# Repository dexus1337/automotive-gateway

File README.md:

# Automotive Gateway: Multi-Bus ECU Interface, MitM Filter & Telemetry Board

[-green.svg)]()

An automotive-grade, multi-protocol vehicle network interface, Man-in-the-Middle (MitM) filter, and wireless telemetry gateway. Rather than focusing on CAN alone, this board provides full hardware integration for **all three common automotive ECU communication methods**:
1. **High-Speed CAN (HS-CAN / CAN FD)**
2. **Fault-Tolerant Low-Speed CAN (FT-CAN)**
3. **K-Line / LIN (ISO 9141-2 / ISO 14230 / LIN 2.x)**

All three protocols are driven by two dedicated 32-bit ARM Cortex-M4 microcontrollers and an ESP32 wireless co-processor, featuring dual isolated channels per protocol.

---

## 📑 Table of Contents

- [Overview](#-overview)
- [Operating Modes: Normal vs. MitM](#-operating-modes-normal-vs-mitm)
- [Power Management & Auto-Wake Architecture](#-power-management--auto-wake-architecture)
- [Key Features](#-key-features)
- [System Architecture](#-system-architecture)
- [Hardware & Functional Zones](#-hardware--functional-zones)
- [Pinout & Interface Definitions](#-pinout--interface-definitions)
- [Jumper Configuration Guide](#-jumper-configuration-guide)
- [Bill of Materials (BOM) Summary](#-bill-of-materials-bom-summary)
- [PCB Layout & Physical Specifications](#-pcb-layout--physical-specifications)
- [Getting Started & Flashing Guide](#-getting-started--flashing-guide)
- [Hardware Attribution](#-hardware-attribution)

---

## 🛠 Overview

Modern vehicle architectures rely on three primary communication standards to interconnect Electronic Control Units (ECUs) across various vehicle domains:
- **High-Speed CAN (HS-CAN / CAN FD)**: Up to 1 Mbps (CAN FD capable up to 5 Mbps) for latency-critical powertrain, drivetrain, braking, ABS, and chassis control.
- **Fault-Tolerant Low-Speed CAN (FT-CAN)**: Up to 125 kbps for robust body control, doors, lighting, climate (HVAC), and convenience systems, featuring automatic single-wire fallback upon bus faults.
- **K-Line / LIN (ISO 9141-2 / ISO 14230 / LIN 2.x)**: Bidirectional single-wire 12V automotive bus (up to 20 kbaud) universally used for OBD-II legacy diagnostics, ECU bench reflashing, instrumentation, and LIN sub-busses.

The **Automotive Gateway** provides a unified hardware platform equipped with dedicated transceivers for all three physical layers. It eliminates the need for separate diagnostic interfaces or multiple conversion dongles, serving as a comprehensive tool for active multi-bus communication, real-time message filtering, frame modification, diagnostic proxying, and wireless telemetry streaming via Wi-Fi and Bluetooth BLE.

---

## ⚙️ Operating Modes: Normal vs. MitM

The board features dual physical transceiver channels per communication method (Channel 1 and Channel 2), supporting two primary operating modes:

```
─────────────────────────────────────────────────────────────────────────────────────────────
 Mode 1: Normal Mode (Standalone Additional ECU / Gateway)
 [ Vehicle Network ] ◄──► ( Channel 1 ) ◄──► [ Dual-STM32 + ESP32 ] (Reads & Sends on Busses)

 Mode 2: In-line Man-in-the-Middle Mode (MitM Filter / Message Modification)
 [ Vehicle Network ] ◄──► ( Channel 1 ) ◄──► [ Real-Time Filter ] ◄──► ( Channel 2 ) ◄──► [ Target ECU ]
─────────────────────────────────────────────────────────────────────────────────────────────
```

### 1. Normal Mode (Standalone ECU)
> [!NOTE]
> **There is no listen-only mode.** In Normal Mode, the Automotive Gateway acts as an active, standalone, additional ECU on the vehicle networks.

- **Bi-directional Bus Access**: The gateway actively reads incoming data and transmits outgoing messages on the connected vehicle busses across all three supported physical interfaces (HS-CAN, FT-CAN, and K-Line/LIN).
- **Core Functions**:
  - Functions as an additional standalone ECU node directly participating on the network.
  - Broadcasts custom telemetry, control frames, or simulated sensor messages onto the bus.
  - Sends diagnostic requests (OBD-II, UDS / ISO 14229, KWP2000 / ISO 14230) to other vehicle ECUs and receives responses.
  - Acts as a bi-directional wireless gateway, streaming live multi-bus metrics and receiving remote commands over Wi-Fi (WebSockets, MQTT, REST) or Bluetooth LE.
- **Bus Connectivity**: Connects to the vehicle network via Channel 1 (`CAN-HS1`, `CAN-FT1`, and/or `K-LINE1 Pin 1`). Channel 2 can interface with a second independent vehicle bus, an auxiliary bench network, or remain unpopulated.

### 2. Man-in-the-Middle (MitM) Mode (In-line Filter & Message Modification)
- **Operation**: The gateway is inserted physically in-line between the vehicle wiring harness and a specific target Electronic Control Unit (ECU).
  - **Channel 1 (Network side)**: Connected to the main vehicle bus (`CAN-HS1`, `CAN-FT1`, or `K-LINE1 Pin 1`).
  - **Channel 2 (ECU side)**: Connected directly to the target ECU (`CAN-HS2`, `CAN-FT2`, or `K-LINE1 Pin 2`).
- **Core Functions**:
  - **Message Filtering**: Intercepts bidirectional communications in real time with sub-millisecond determinism to selectively filter out, block, or suppress unwanted messages, diagnostic requests, or forbidden IDs.
  - **Message Modification**: Inspects packets on the fly and modifies payload bytes, alters sensor values (e.g., vehicle speed, odometer, torque parameters), remaps frame IDs, recalculates CRCs/checksums, and retransmits them downstream.
  - **ECU Bench Testing & Security**: Allows fuzzing, spoofing responses, and security validation of a targeted ECU without injecting malformed or test frames into the rest of the vehicle.

---

## ⚡ Power Management & Auto-Wake Architecture

The board features an intelligent automotive power supply designed for both permanent vehicle installation and portable diagnostic use:

```
                        +12V Battery Input (12V1 Pin 1)
                                      │
                         [ D5: SMCJ24CA 24V TVS ]
                                      │
                         [ Q1: AO3401A P-MOSFET ]
                                      │ (12V_Switched)
                                      ▼
                        [ U8: LM2596S-5 Buck Conv ] ──► +5V Rail
                                      │
                        [ U9: AMS1117-3.3 LDO ]    ──► +3.3V Logic Rail
```

### Intelligent Sleep & Auto-Wake Circuit
To prevent 12V battery drain when permanently installed in a vehicle, the module features an ultra-low quiescent sleep circuit:
1. **Sleep State**: The high-side P-channel MOSFET (`Q1`) cuts +12V power to the buck converter (`U8`), completely disabling the 5V and 3.3V rails. The microcontrollers and ESP32 consume **zero current**.
2. **Wake-up Trigger**: The Fault-Tolerant CAN transceiver (`U6`, NXP TJA1055T) remains powered directly from the protected 12V battery rail in ultra-low quiescent standby mode. Upon detecting bus activity on FT-CAN Channel 1, `U6` asserts its `INH` pin HIGH, pulling the gate of N-channel MOSFET `Q2` high via dual Schottky diode `D4`.
3. **Power Latch (Keep-Alive)**: `Q2` activates, pulling `Q1`'s gate low to turn ON the system power rails. Once booted, MCU 1 (`U1`) and MCU 2 (`U2`) assert their respective keep-alive GPIOs (`PC13` via `D3`) to latch power continuously.
4. **Controlled Shutdown**: When vehicle network traffic ceases, the firmware prepares for safe shutdown and de-asserts `PC13`, allowing the board to return to sleep.
5. **Always-On Override (`J3`)**: Installing a jumper on header `J3` (`JP_ALWAYS_ON`) bypasses the auto-wake logic and holds the board permanently powered whenever +12V is present.

---

## ✨ Key Features

- **Dual ARM Cortex-M4 Processing Core**:
  - Two dedicated **STM32F405RGTx** microcontrollers running at **168 MHz** (1 MB Flash, 192 KB SRAM each).
  - **MCU 1 (`U1`)**: Dedicated Low-Speed Fault-Tolerant CAN controller (`CAN1` & `CAN2`).
  - **MCU 2 (`U2`)**: Dedicated High-Speed CAN (`CAN1` & `CAN2`) and Dual K-Line controller (`USART1` & `USART6`).
- **Direct High-Speed Inter-MCU Link**:
  - Dedicated hardware UART bus connecting MCU 1 and MCU 2 (`PC10` / `PC11`) for deterministic cross-bus message passing without co-processor latency.
- **All 3 Common Automotive ECU Physical Layers Supported (Dual Channels Each)**:
  - **High-Speed CAN (HS-CAN / CAN FD)**: 2× NXP `TJA1044GT-3` transceivers (ISO 11898-2:2016, CAN FD ready up to 5 Mbps) with switchable 120 Ω bus termination.
  - **Fault-Tolerant Low-Speed CAN (FT-CAN)**: 2× NXP `TJA1055T/3` transceivers (ISO 11898-3, up to 125 kbps) with single-wire fallback and automatic wake-up signaling.
  - **Dual K-Line / LIN (ISO 9141-2 / ISO 14230 / LIN 2.x)**: 2× NXP `TJA1021xT` transceivers (LIN 2.2A / SAE J2602) supporting OBD-II and KWP2000 diagnostic lines up to 20 kbaud.
- **High-Precision External Quartz Clocking (HSE)**:
  - Dedicated 8.000 MHz SMD-3225 4-pin quartz crystals (`Y1`, `Y2`) with 15 pF C0G load capacitors (`C40`–`C43`) for both STM32F405 MCUs.
  - Automotive-grade $\pm 10\,\text{ppm}$ clock accuracy, eliminating internal RC oscillator frequency drift across automotive temperature ranges.
  - **Zero-Error Baud Rate Timing**: Derives an exact 42 MHz APB1 peripheral clock, achieving $0.000\%$ timing error for the critical **83.3333 kBd** Fault-Tolerant CAN standard ($\text{BRP}=28$, $18\,T_q$, $83.33\%$ sample point) as well as exact bit rates for 100k, 125k, 250k, 500k, and 1 MBd HS-CAN / CAN FD.
- **Wireless Telemetry Co-Processor**:
  - **ESP32-WROOM-32UE** module with 2.4 GHz Wi-Fi (802.11 b/g/n) and Bluetooth v4.2 BR/EDR & BLE.
  - Integrated U.FL external antenna connector for high-gain antenna placement inside vehicle dashboards or engine bays.
  - Dual independent high-speed UART links connecting to MCU 1 and MCU 2.
- **User Interface & Diagnostic Feedback**:
  - Onboard RGB Status LED (`D6`, SMD 1210) driven by ESP32 GPIOs for mode, packet activity, and error signaling.
  - Tactile push buttons for ESP32 hardware `RESET` and `BOOT` (GPIO0).
- **Automotive Protection & Regulation**:
  - Automotive transient voltage suppressor (`D5`, SMCJ24CA bidirectional TVS).
  - P-channel MOSFET (`Q1`, AO3401A) reverse polarity and high-side power switching.
  - 12V Zener (`D1`, MMSZ12T1G) Vgs gate overvoltage clamp.
  - High-efficiency switching buck regulator (`U8`, LM2596S-5, 3A capacity).
  - Low-dropout linear regulator (`U9`, AMS1117-3.3, 1A capacity).
  - Ferrite bead filtering (`FB1`, `FB2`) on analog power supplies (`VDDA`).

---

## 📐 System Architecture

```
                                  +12V AUTOMOTIVE BATTERY (12V1)
                                                │
                          ┌─────────────────────┴─────────────────────┐
                          ▼                                           ▼
             [ SMCJ24CA 24V TVS Clamp ]                  [ AO3401A P-MOSFET Switch ]
                          │                                           │ (12V_Switched)
                          │                                           ▼
                          │                              [ LM2596S-5 Buck Regulator ] ──► +5V Rail
                          │                                           │
                          │                              [ AMS1117-3.3 LDO Regulator] ──► +3.3V Rail
                          │                                           │
         ┌────────────────┴───────────────────────────────────────────┴────────────────────────┐
         │                                                            │                        │
         ▼                                                            ▼                        ▼
┌───────────────────────────────┐               ┌───────────────────────────────┐   ┌──────────────────────┐
│      STM32F405 #1 (MCU 1)     │               │      STM32F405 #2 (MCU 2)     │   │   ESP32-WROOM-32UE   │
│   Low-Speed Fault-Tolerant    │◄─────────────►│     High-Speed CAN & K-Line   │   │   Wireless Gateway   │
│   CAN Controller (168 MHz)    │  Direct UART  │     Controller (168 MHz)      │   │   (Wi-Fi / BT / BLE) │
└──────┬─────────────────┬──────┘   (PC10/PC11) └──────┬─────────────────┬──────┘   └───────┬──────┬───────┘
       │ (CAN1)          │ (CAN2)                      │ (CAN1)          │ (CAN2)           │      │
       ▼                 ▼                             ▼                 ▼                  │      │
 ┌───────────┐     ┌───────────┐                 ┌───────────┐     ┌───────────┐            │      │
 │  TJA1055T │     │  TJA1055T │                 │ TJA1044GT │     │ TJA1044GT │      UART1 │      │ UART2
 │ (FT-CAN1) │     │ (FT-CAN2) │                 │ (HS-CAN1) │     │ (HS-CAN2) │   (PA2/PA3)│      │(PA2/PA3)
 └─────┬─────┘     └─────┬─────┘                 └─────┬─────┘     └─────┬─────┘            │      │
       │                 │                             │                 │                  │      │
       ▼                 ▼                             ▼                 ▼                  │      │
 [  CAN-FT1  ]     [  CAN-FT2  ]                 [  CAN-HS1  ]     [  CAN-HS2  ]            ▼      ▼
 (Channel 1)       (Channel 2)                   (Channel 1)       (Channel 2)          [ Independent ]
  Normal / MitM     Normal / MitM                 Normal / MitM     Normal / MitM       [ UART Links  ]
                                                       │                 │                     │
                                                 ┌─────┴─────┐     ┌─────┴─────┐               ▼
                                                 │JP-CAN-HS1 │     │JP-CAN-HS2 │        [ RGB LED (D6) ]
                                                 │(120Ω Term)│     │(120Ω Term)│        [ GPIO25/26/27 ]
                                                 └───────────┘     └───────────┘
                                                
                                                [ MCU 2 UARTs (USART6 / USART1) ]
                                                               │
                                                   ┌───────────┴───────────┐
                                                   ▼                       ▼
                                             ┌───────────┐           ┌───────────┐
                                             │ TJA1021xT │           │ TJA1021xT │
                                             │ (K-Line 1)│           │ (K-Line 2)│
                                             └─────┬─────┘           └─────┬─────┘
                                                   │                       │
                                                   ▼                       ▼
                                             [        K-LINE1 Header       ]
                                             [  Pin 1: Ch 1  |  Pin 2: Ch 2]
                                             [         Normal / MitM       ]
```

---

## 🔍 Hardware & Functional Zones

### Zone 1: Power Regulation, Switching & Protection
- **Power Input**: Connector `12V1` (Pin 1: `+12V_Protected`, Pin 2: `GND`).
- **Protection**:
  - `D5` (`SMCJ24CA`): Bidirectional TVS diode clamps automotive load-dump surges.
  - `Q1` (`AO3401A`): P-channel MOSFET provides high-side switching and reverse-polarity protection.
  - `D1` (`MMSZ12T1G`): 12V Zener clamps gate-source voltage ($V_{GS}$) of `Q1`.
  - `D2` (`SS34`): 3A 40V Schottky barrier rectifier for the buck switching regulator.
- **Power Switching Logic**:
  - `Q2` (`2N7002`): N-channel MOSFET drives `Q1`'s gate low to enable system power.
  - `D4` (`BAT54C`): Dual diode ORs the auto-wake signal from `U6` (`INH`) and `J3` (`ALWAYS_ON`).
  - `D3` (`BAT54C`): Dual diode ORs keep-alive latch signals from MCU 1 (`U1 PC13`) and MCU 2 (`U2 PC13`).
- **Regulators**:
  - `U8` (`LM2596S-5`): High-efficiency 5V 3A step-down switching regulator.
  - `U9` (`AMS1117-3.3`): 3.3V 1A linear LDO regulator for logic and radio power.

### Zone 2: MCU #1 – Low-Speed Fault-Tolerant CAN Core
- **Microcontroller**: `U1` (`STM32F405RGTx` LQFP-64, ARM Cortex-M4 @ 168 MHz).
- **External Clock Source**: `Y1` (8.000 MHz SMD-3225 4-pin crystal on `PH0-OSC_IN` [Pin 5] and `PH1-OSC_OUT` [Pin 6]) with 15 pF load capacitors `C40` & `C41`.
- **Transceivers**: `U6` & `U7` (`NXP TJA1055T/3` SOIC-14).
- **Pin Mapping**:
  - `FT-CAN 1` (Channel 1): RX = `PA11`, TX = `PA12`, Wake Inhibit = `U6 INH`, Error = `U6 ~ERR` (`PB11` via `R8`), Standby = `PC7`, Enable = `PC8`.
  - `FT-CAN 2` (Channel 2): RX = `PB5`, TX = `PB6`, Error = `U7 ~ERR` (`PB12` via `R9`), Standby/Enable = Tied to 3.3V.
  - Power Keep-Alive: `PC13` (controls `Q2` gate via `D3`).
  - Inter-MCU Link: TX = `PC10`, RX = `PC11` (connects directly to MCU 2).
  - ESP32 Link: TX = `PA2`, RX = `PA3` (connects to ESP32 `IO19` / `IO18`).
  - SWD Debug: SWCLK = `PA14`, SWDIO = `PA13`, NRST = `Pin 7`.

### Zone 3: MCU #2 – High-Speed CAN & Dual K-Line Core
- **Microcontroller**: `U2` (`STM32F405RGTx` LQFP-64, ARM Cortex-M4 @ 168 MHz).
- **External Clock Source**: `Y2` (8.000 MHz SMD-3225 4-pin crystal on `PH0-OSC_IN` [Pin 5] and `PH1-OSC_OUT` [Pin 6]) with 15 pF load capacitors `C42` & `C43`.
- **High-Speed Transceivers**: `U4` & `U5` (`NXP TJA1044GT-3` SOIC-8).
- **K-Line Transceivers**: `U10` & `U11` (`NXP TJA1021xT` SOIC-8).
- **Pin Mapping**:
  - `HS-CAN 1` (Channel 1): RX = `PA11`, TX = `PA12`.
  - `HS-CAN 2` (Channel 2): RX = `PB5`, TX = `PB6`.
  - `K-Line 1` (Channel 1, `U10`): TX = `PC6` (`USART6_TX`), RX = `PC7` (`USART6_RX`).
  - `K-Line 2` (Channel 2, `U11`): TX = `PA9` (`USART1_TX`), RX = `PA10` (`USART1_RX`).
  - Power Keep-Alive: `PC13` (controls `Q2` gate via `D3`).
  - Inter-MCU Link: TX = `PC10`, RX = `PC11` (connects directly to MCU 1).
  - ESP32 Link: TX = `PA2`, RX = `PA3` (connects to ESP32 `IO17` / `IO16`).
  - SWD Debug: SWCLK = `PA14`, SWDIO = `PA13`, NRST = `Pin 7`.

### Zone 4: ESP32 Wireless Telemetry Co-Processor
- **Module**: `U3` (`ESP32-WROOM-32UE` with external U.FL antenna jack).
- **Pin Mapping**:
  - Link to MCU 1: RX = `IO19`, TX = `IO18`.
  - Link to MCU 2: RX = `IO16`, TX = `IO17`.
  - Programming Port: `TXD0` (`Pin 35`), `RXD0` (`Pin 34`), `EN` (`Pin 3`), `IO0` (`Pin 25`).
  - RGB Status LED (`D6`): Red = `IO25`, Green = `IO26`, Blue = `IO27`.
  - Hardware Buttons: `RESET` (pulls `EN` low), `BOOT` (pulls `IO0` low).

---

## 🔌 Pinout & Interface Definitions

All external signals, power, bus lines, and programming ports are brought out to standardized 2.54 mm pin headers:

### 1. Automotive Power Header (`12V1`)
| Pin | Silkscreen | Net Name | Voltage Range | Description |
| :---: | :--- | :--- | :--- | :--- |
| **1** | *(Square pad)* | `/12V_Protected` | +7.0V to +18.0V DC | Primary Automotive Battery/Ignition Supply |
| **2** | `GND` | `/GND` | 0V | Common Chassis / System Ground |

### 2. High-Speed CAN Connectors
| Connector | Pin | Silkscreen | Signal | Transceiver Pin | Function / Topology |
| :--- | :---: | :--- | :--- | :--- | :--- |
| **`CAN-HS1`** | 1 | `CAN-HS-L1` | `CAN_L` | `U4` Pin 6 | **Channel 1**: Normal Mode (Vehicle Bus) / MitM Input |
| | 2 | `CAN-HS-H1` | `CAN_H` | `U4` Pin 7 | **Channel 1**: Normal Mode (Vehicle Bus) / MitM Input |
| **`CAN-HS2`** | 1 | `CAN-HS-L2` | `CAN_L` | `U5` Pin 6 | **Channel 2**: MitM Output (Target ECU) / Secondary Bus |
| | 2 | `CAN-HS-H2` | `CAN_H` | `U5` Pin 7 | **Channel 2**: MitM Output (Target ECU) / Secondary Bus |

### 3. Fault-Tolerant Low-Speed CAN Connectors
| Connector | Pin | Silkscreen | Signal | Transceiver Pin | Function / Topology |
| :--- | :---: | :--- | :--- | :--- | :--- |
| **`CAN-FT1`** | 1 | `CAN-FT-L1` | `CAN_L` | `U6` Pin 12 | **Channel 1**: Normal Mode (Vehicle Bus) / MitM Input / Auto-Wake |
| | 2 | `CAN-FT-H1` | `CAN_H` | `U6` Pin 11 | **Channel 1**: Normal Mode (Vehicle Bus) / MitM Input / Auto-Wake |
| **`CAN-FT2`** | 1 | `CAN-FT-L2` | `CAN_L` | `U7` Pin 12 | **Channel 2**: MitM Output (Target ECU) / Secondary Bus |
| | 2 | `CAN-FT-H2` | `CAN_H` | `U7` Pin 11 | **Channel 2**: MitM Output (Target ECU) / Secondary Bus |

### 4. Dual K-Line / LIN Connector (`K-LINE1`)
| Pin | Silkscreen | Connected Transceiver | MCU Peripheral | Operating Voltage | Function / Topology |
| :---: | :--- | :--- | :--- | :---: | :--- |
| **1** | *(Pin 1)* | `U10` (TJA1021xT Pin 6) | MCU 2 `USART6` (`PC6`/`PC7`) | 12V Automotive | **Channel 1**: Normal Mode (OBD-II / Harness) / MitM Input |
| **2** | `K-LINE2` | `U11` (TJA1021xT Pin 6) | MCU 2 `USART1` (`PA9`/`PA10`)| 12V Automotive | **Channel 2**: MitM Output (Target ECU) / Secondary K-Line |

### 5. Programming & SWD Debug Headers
| Header | Pin 1 | Pin 2 | Pin 3 | Pin 4 | Pin 5 | Target IC |
| :--- | :---: | :---: | :---: | :---: | :---: | :--- |
| **`STM_FLASH1`** | `+3.3V` | `GND` | `SWDIO` (`PA13`) | `NRST` | `SWCLK` (`PA14`) | MCU 1 (STM32F405 FT-CAN Core) |
| **`STM_FLASH2`** | `+3.3V` | `GND` | `SWDIO` (`PA13`) | `NRST` | `SWCLK` (`PA14`) | MCU 2 (STM32F405 HS-CAN & K-Line Core) |
| **`ESP_FLASH1`** | `TXD0` | `RXD0` | `ESP_EN` | `GPIO0 (BOOT)` | `GND` | ESP32-WROOM-32UE Wireless Co-Processor |

---

## 🎛 Jumper Configuration Guide

| Jumper Header | Silkscreen | Function | Jumper Installed (Closed) | Jumper Removed (Open) | Default |
| :--- | :--- | :--- | :--- | :--- | :---: |
| **`J3`** | `ALWAYS_ON` | Power Control Mode | **Always-On**: Board powered whenever 12V is connected. | **Auto-Sleep / Wake**: Board sleeps; wakes on FT-CAN activity. | *Open* |
| **`JP-CAN-HS1`** | *(Near CAN-HS1)* | HS-CAN 1 Bus Termination | **120 Ω Enabled** (`R5` connected across H and L). | **Unterminated** (For active vehicle bus connection). | *Open* |
| **`JP-CAN-HS2`** | *(Near CAN-HS2)* | HS-CAN 2 Bus Termination | **120 Ω Enabled** (`R6` connected across H and L). | **Unterminated** (For active vehicle bus connection). | *Open* |

> [!TIP]
> - In **Normal Mode** connected to an active vehicle network, keep `JP-CAN-HS1` and `JP-CAN-HS2` **OPEN** because the vehicle network already provides the required split 60 Ω termination.
> - In **MitM Mode** or bench-testing an isolated ECU, install the jumper on the isolated segment (`JP-CAN-HS2`) to provide the required 120 Ω termination for CAN transceivers.

---

## 📦 Bill of Materials (BOM) Summary

| Reference Designator | Component Value | Package / Footprint | Qty | Description |
| :--- | :--- | :--- | :---: | :--- |
| **`U1`, `U2`** | `STM32F405RGTx` | LQFP-64 (10×10 mm, 0.5 mm pitch) | 2 | 32-bit ARM Cortex-M4 MCU (168 MHz, 1MB Flash, 192KB RAM) |
| **`U3`** | `ESP32-WROOM-32UE` | RF Module (18×25.5 mm) | 1 | Dual-Core Wi-Fi & BLE Co-Processor (U.FL antenna) |
| **`U4`, `U5`** | `TJA1044GT-3` | SOIC-8 (3.9×4.9 mm, 1.27 mm pitch) | 2 | High-Speed CAN Transceiver (CAN FD capable, 5 Mbps) |
| **`U6`, `U7`** | `TJA1055T/3` | SOIC-14 (3.9×8.7 mm, 1.27 mm pitch) | 2 | Fault-Tolerant Low-Speed CAN Transceiver (125 kbps) |
| **`U10`, `U11`** | `TJA1021xT` | SOIC-8 (3.9×4.9 mm, 1.27 mm pitch) | 2 | LIN 2.2A / K-Line Physical Transceiver (ISO 9141-2) |
| **`U8`** | `LM2596S-5` | TO-263-5 (D2PAK) | 1 | 5V 3A Step-Down Switching Buck Regulator |
| **`U9`** | `AMS1117-3.3` | SOT-223-3 | 1 | 3.3V 1A Low-Dropout Linear Regulator |
| **`Q1`** | `AO3401A` | SOT-23 | 1 | P-Channel MOSFET (-30V, -4.2A, Power Switch / Rev. Pol.) |
| **`Q2`** | `2N7002` | SOT-23 | 1 | N-Channel Signal MOSFET (60V, 115mA, Gate Driver) |
| **`D1`** | `MMSZ12T1G` | SOD-123 / SMA | 1 | 12V 500mW Zener Diode (MOSFET Vgs Clamp) |
| **`D2`** | `SS34` | DO-214AC (SMA) | 1 | 3A 40V Schottky Barrier Rectifier Diode |
| **`D3`, `D4`** | `BAT54C` | SOT-23 | 2 | Dual Common-Cathode 30V Schottky Diodes |
| **`D5`** | `SMCJ24CA` | DO-214AB (SMC) | 1 | 24V 1500W Bidirectional TVS Surge Clamping Diode |
| **`D6`** | `LED_RGBA` | SMD 1210 (Common Anode) | 1 | RGB Status & Diagnostic Indicator LED |
| **`L1`** | `33-68 µH` | Bourns SRP6060FA (SMD Inductor) | 1 | Power Inductor for LM2596 Buck Converter |
| **`FB1`, `FB2`** | `Ferrite Bead` | SMD 0805 | 2 | High-Frequency Analog Noise Filtering Beads (`VDDA`) |
| **`Y1`, `Y2`** | `8.000 MHz` | SMD-3225 4-Pin (HandSoldering) | 2 | High-Precision HSE Quartz Crystals (±10 ppm, 15 pF CL) |
| **`RESET`, `BOOT`** | `PTS636Sx25` | Tactile Switch SMD | 2 | Push buttons for ESP32 Hardware Reset & Boot Mode |
| **`R5`, `R6`** | `120 Ω` | SMD 0805 (1%) | 2 | High-Speed CAN Bus Termination Resistors |
| **`R1` - `R4`** | `560 Ω` | SMD 0805 (1%) | 4 | Fault-Tolerant CAN Bias/Termination Resistors |
| **`R20` - `R22`** | `1 kΩ` | SMD 0805 | 3 | RGB LED Current Limiting Resistors |
| **`R7`, `R13`** | `100 kΩ` | SMD 0805 | 2 | Gate & Inhibit Pull-Down Resistors |
| **`R8` - `R12`, `R14` - `R19`** | `10 kΩ` | SMD 0805 | 11 | Pull-Up / Pull-Down / Logic Bias Resistors |
| **`C14`** | `100 µF` | SMD Aluminum Electrolytic (6.3×7.7 mm)| 1 | 12V Switched Input Decoupling |
| **`C5`, `C32`** | `220 µF` | EIA-6032-28 (Kemet C Tantalum) | 2 | 5V and 3.3V Output Smoothing Capacitors |
| **`C8` - `C11`** | `5.6 nF` | SMD 0805 | 4 | FT-CAN Bus Filter Capacitors |
| **`C12`, `C13`, `C20`, `C29`** | `2.2 µF` | SMD 0805 | 4 | MCU VCAP Core Decoupling Capacitors |
| **`C26`, `C27`** | `4.7 µF` | SMD 0805 | 2 | Power Rail Filtering Capacitors |
| **`C25`, `C28`, `C34`** | `1 µF` | SMD 0805 | 3 | Logic Decoupling Capacitors |
| **`C1` - `C4`, `C6`, `C7`, `C15` - `C19`, `C21` - `C24`, `C30`, `C31`, `C33`, `C35` - `C39` | `100 nF` | SMD 0805 | 22 | Local IC Decoupling Ceramic Capacitors |
| **`C40` - `C43`** | `15 pF` | SMD 0805 (C0G/NP0) | 4 | Crystal Load Capacitors (HSE Oscillators) |
| **`12V1`, `J3`, `CAN-HS1/2`, `CAN-FT1/2`, `JP-CAN-HS1/2`, `K-LINE1`** | `Conn_01x02_Pin` | 2.54 mm Pin Header (1×02) | 8 | External Power, Bus & Termination Headers |
| **`STM_FLASH1`, `STM_FLASH2`, `ESP_FLASH1`** | `Conn_01x05_Pin` | 2.54 mm Pin Header (1×05) | 3 | Programming and SWD Debug Headers |
| **`H1` - `H4`** | `MountingHole_Pad` | 3.2 mm Diameter (M3 Pad) | 4 | Grounded Chassis M3 Mounting Holes |

---

## 📏 PCB Layout & Physical Specifications

- **Dimensions**: **101.60 mm × 88.90 mm** (4.00" × 3.50")
- **Corner Fillet**: 2.0 mm corner radius
- **Layer Count**: **2 Copper Layers** (`F.Cu` Top Layer, `B.Cu` Bottom Layer)
- **Board Thickness**: Standard 1.6 mm FR4
- **Copper Thickness**: 1 oz (35 µm)
- **Ground Planes**: Continuous, low-impedance ground fill on the bottom layer with stitched return paths for high-frequency CAN differential lines.
- **Mounting**: 4× grounded M3 mounting holes located at the corners.
- **Footprint Pitch**: Standard 0805 (2012 metric) passive SMD footprints for reliable hand-soldering and prototype assembly.
- **Total Footprint Count**: 109 placed board footprints.

---

## 🚀 Getting Started & Flashing Guide

### 1. Opening the KiCad Project
1. Install **KiCad 8.0** or newer.
2. Clone the repository:
   ```bash
   git clone https://github.com/dexus1337/automotive-gateway.git
   ```
3. Open `automotive-gateway.kicad_pro` to inspect or modify schematics and PCB layout.

### 2. Flashing STM32 Microcontrollers (MCU 1 & MCU 2)
The board features independent 5-pin SWD headers for each STM32F405 MCU:
- **MCU 1 (Low-Speed FT-CAN Core)**: Connect an ST-LINK V2/V3 to `STM_FLASH1` (`3.3V`, `GND`, `SWDIO`, `NRST`, `SWCLK`).
- **MCU 2 (High-Speed CAN & K-Line Core)**: Connect an ST-LINK to `STM_FLASH2` (`3.3V`, `GND`, `SWDIO`, `NRST`, `SWCLK`).
- Compatible toolchains: **STM32CubeIDE**, **PlatformIO** (`ststm32`), or **Keil MDK**.

### 3. Flashing the ESP32 Wireless Co-Processor
1. Connect a 3.3V USB-to-UART adapter to `ESP_FLASH1`:
   - Adapter TX ──► `ESP_RXD` (Pin 2)
   - Adapter RX ──► `ESP_TXD` (Pin 1)
   - Adapter GND ──► `ESP_GND` (Pin 5)
2. Enter Bootloader Mode:
   - Hold down the **`BOOT`** button.
   - Press and release the **`RESET`** button.
   - Release the **`BOOT`** button.
3. Flash using **ESP-IDF**, **esptool.py**, or **PlatformIO** (`espressif32`).

---

## 👤 Hardware Attribution

- **Hardware Design & Engineering**: Hans Lenhard
- **Hardware Revision**: V1.1 (2026)
- **Silkscreen Identification**: `LHE_AUTOGW_11`

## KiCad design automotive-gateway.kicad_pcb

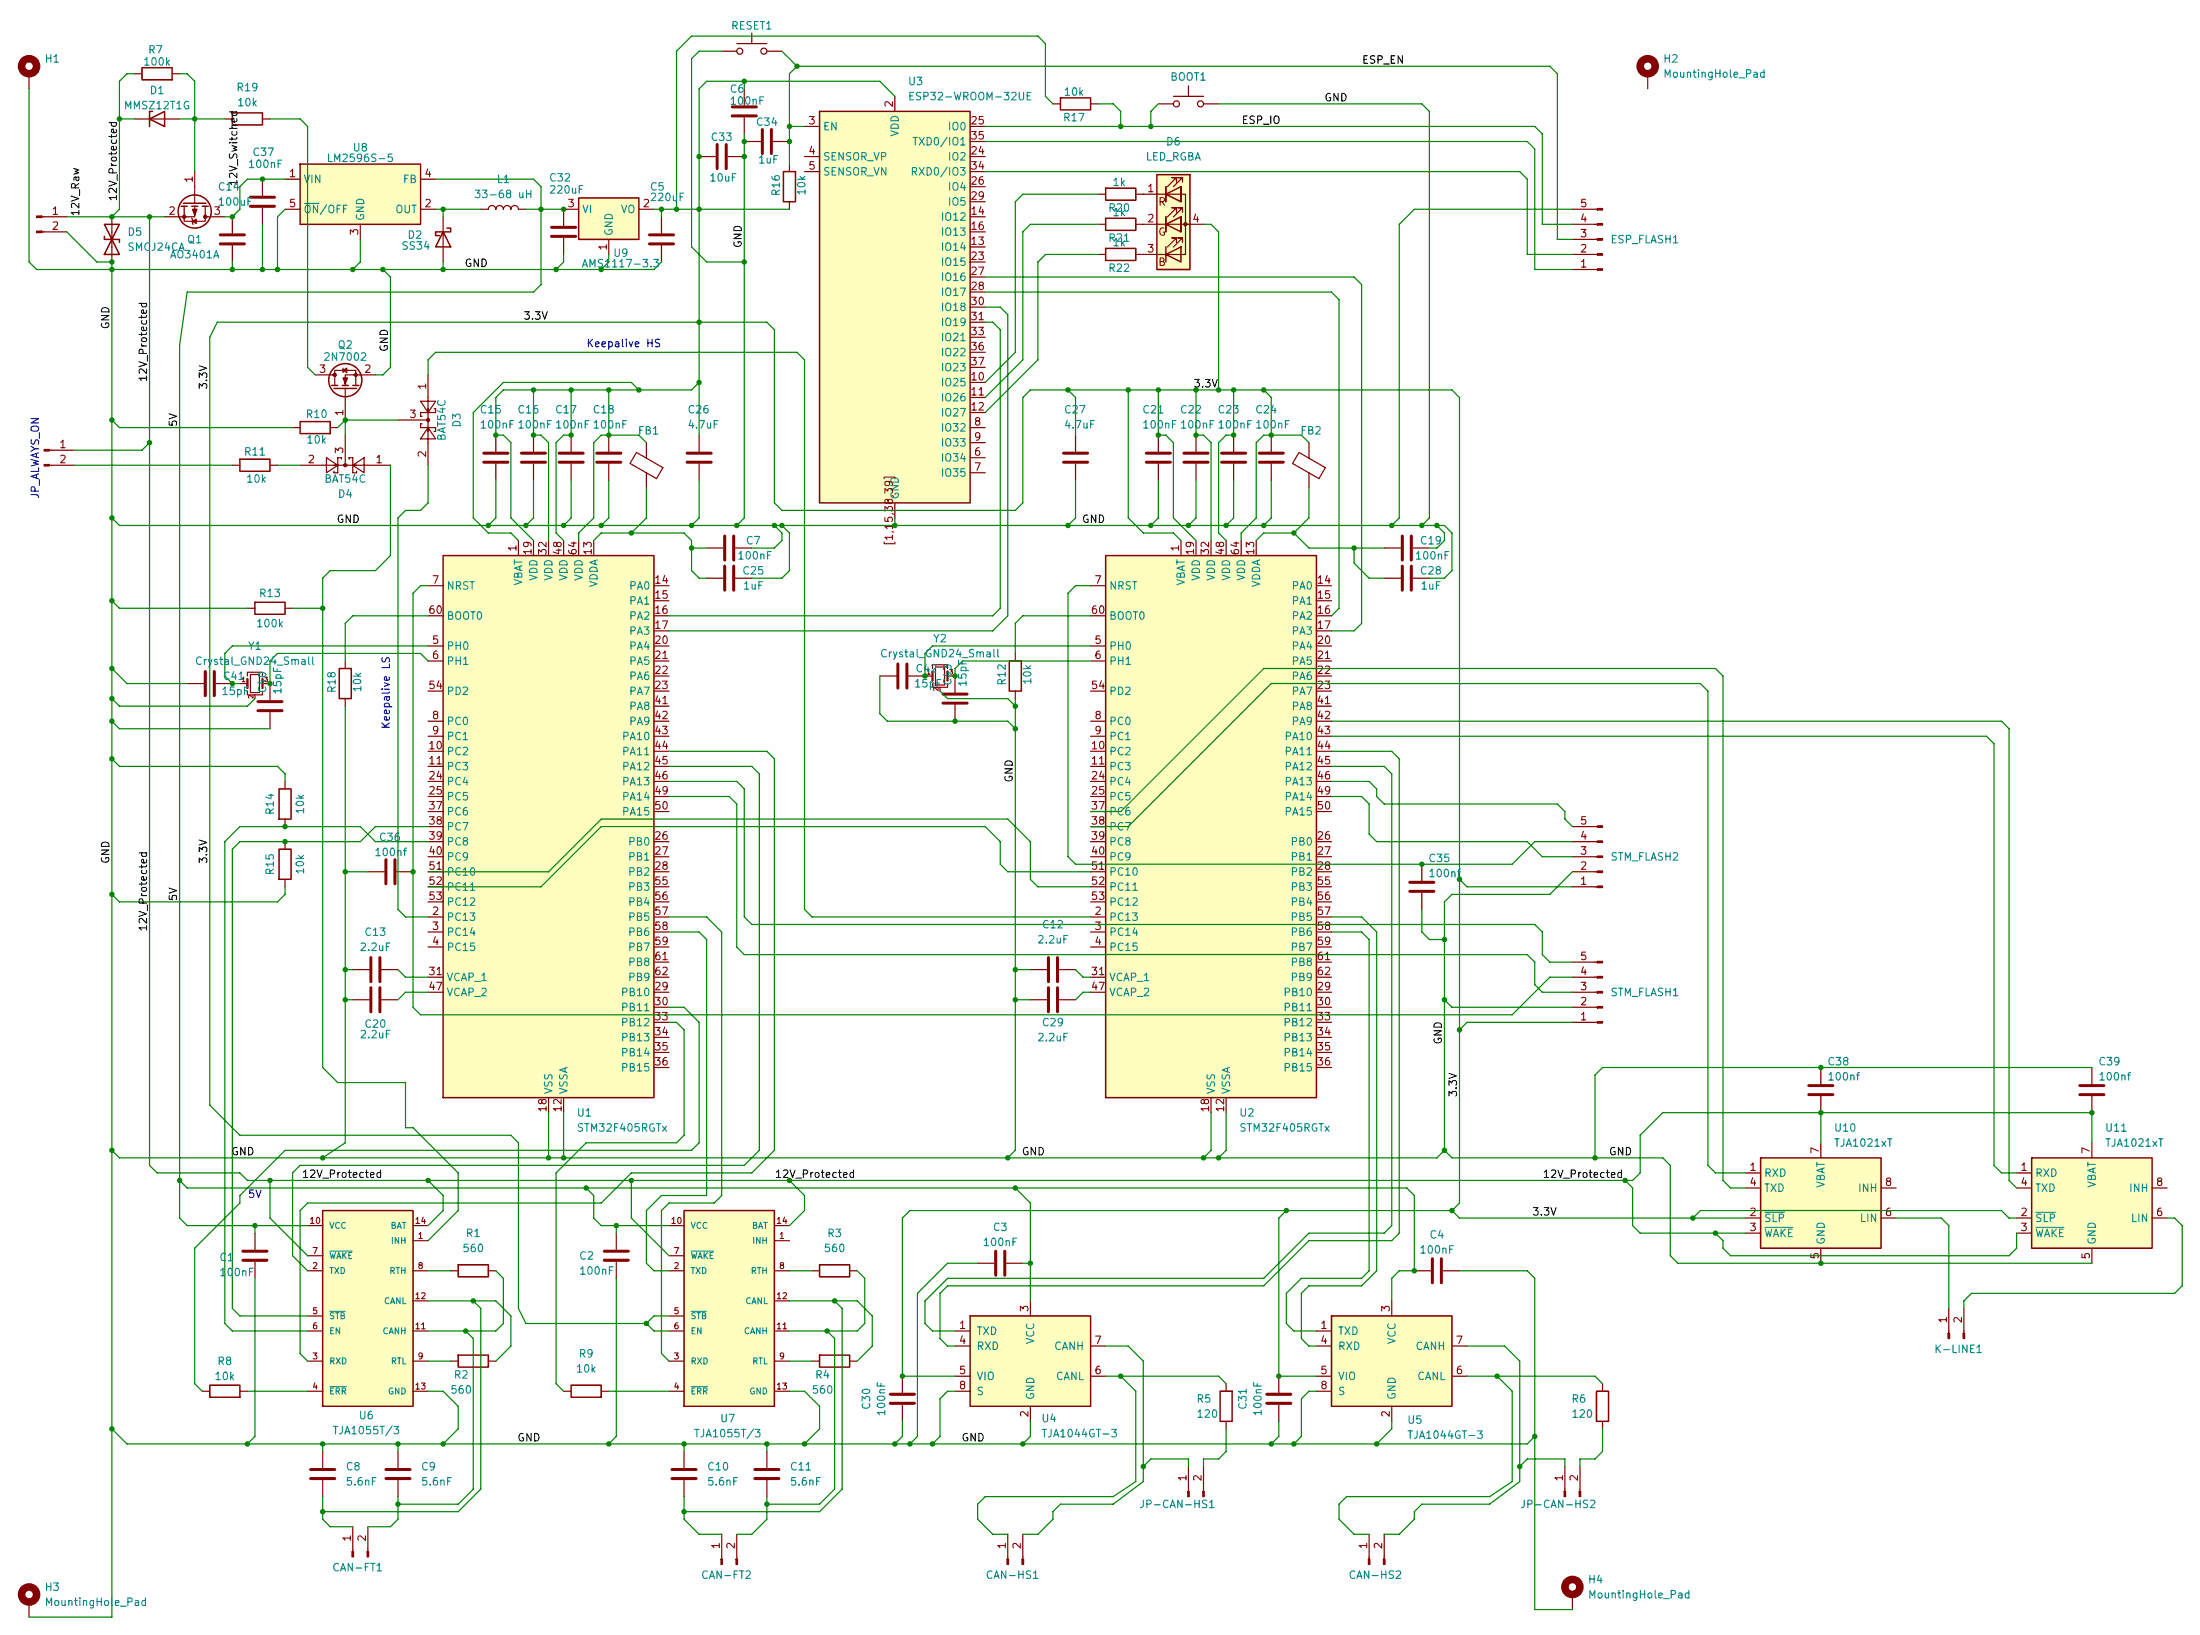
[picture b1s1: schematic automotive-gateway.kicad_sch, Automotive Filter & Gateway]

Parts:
12V1: Conn_01x02_Pin; PinHeader_1x02_P2.54mm_Vertical
BOOT1: ESP_BOOT; SW_Tactile_SPST_NO_Straight_CK_PTS636Sx25SMTRLFS
C1, C2, C3, C4, C6, C7, C15, C16, C17, C18, C19, C21, C22, C23, C24, C30, C31, C37: 100nF; C_0805_2012Metric
C5, C32: 220uF; CP_EIA-6032-28_Kemet-C_HandSolder
C8, C9, C10, C11: 5.6nF; C_0805_2012Metric
C12, C13, C20, C29: 2.2uF; C_0805_2012Metric
C14: 100uF; CP_Elec_6.3x7.7
C25, C28, C34: 1uF; C_0805_2012Metric
C26, C27: 4.7uF; C_0805_2012Metric
C33: 10uF; C_0805_2012Metric
C35, C36, C38, C39: 100nf; C_0805_2012Metric
C40, C41, C42, C43: 15pF; C_0805_2012Metric
CAN-FT1, CAN-FT2: Conn_01x02_Pin; PinHeader_1x02_P2.54mm_Vertical
CAN-HS1, CAN-HS2: Conn_01x02_Pin; PinHeader_1x02_P2.54mm_Vertical
D1: MMSZ12T1G; D_SMA
D2: SS34; D_SMA
D3, D4: BAT54C; SOT-23
D5: SMCJ24CA; D_SMC
D6: LED_RGBA; LED_RGB_1210
ESP_FLASH1: Conn_01x05_Pin; PinHeader_1x05_P2.54mm_Vertical
FB1, FB2: L_0805_2012Metric
H1, H2, H3, H4: MountingHole_Pad; MountingHole_3.2mm_M3_Pad
J3: Conn_01x02_Pin; PinHeader_1x02_P2.54mm_Vertical
JP-CAN-HS1, JP-CAN-HS2: Conn_01x02_Pin; PinHeader_1x02_P2.54mm_Vertical
K-LINE1: Conn_01x02_Pin; PinHeader_1x02_P2.54mm_Vertical
L1: 33-68 uH; L_Bourns_SRP6060FA
Q1: AO3401A; SOT-23
Q2: 2N7002; SOT-23
R1, R2, R3, R4: 560; R_0805_2012Metric
R5, R6: 120; R_0805_2012Metric
R7, R13: 100k; R_0805_2012Metric
R8, R9, R10, R11, R12, R14, R15, R16, R17, R18, R19: 10k; R_0805_2012Metric
R20, R21, R22: 1k; R_0805_2012Metric
RESET1: ESP_RESET; SW_Tactile_SPST_NO_Straight_CK_PTS636Sx25SMTRLFS
STM_FLASH1, STM_FLASH2: Conn_01x05_Pin; PinHeader_1x05_P2.54mm_Vertical
U1, U2: STM32F405RGTx; LQFP-64_10x10mm_P0.5mm
U3: ESP32-WROOM-32UE; ESP32-WROOM-32E
U4, U5: TJA1044GT-3; SOIC-8_3.9x4.9mm_P1.27mm
U6, U7: TJA1055T/3; SOIC-14_3.9x8.7mm_P1.27mm
U8: LM2596S-5; TO-263-5_TabPin3
U9: AMS1117-3.3; SOT-223-3_TabPin2
U10, U11: TJA1021xT; SOIC-8_3.9x4.9mm_P1.27mm
Y1, Y2: Crystal_GND24_Small; Crystal_SMD_3225-4Pin_3.2x2.5mm_HandSoldering

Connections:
/3.3V: C5.2, C6.1, C15.1, C16.1, C17.1, C18.1, C21.1, C22.1, C23.1, C24.1, C26.1, C27.1, C30.1, C31.1, C33.1, D6.4 (A), FB1.2, FB2.2, R16.1, R17.2, STM_FLASH1.1, STM_FLASH2.1, U1.1 (VBAT), U1.19 (VDD), U1.32 (VDD), U1.48 (VDD), U1.64 (VDD), U2.1 (VBAT), U2.19 (VDD), U2.32 (VDD), U2.48 (VDD), U2.64 (VDD), U3.2 (VDD), U4.5 (VIO), U5.5 (VIO), U7.5 (~STB), U7.6 (EN), U9.2 (VO), U10.2 (~SLP), U11.2 (~SLP)
/5V: C1.2, C2.2, C3.1, C4.2, C32.2, L1.2, U4.3 (VCC), U5.3 (VCC), U6.10 (VCC), U7.10 (VCC), U8.4 (FB), U9.3 (VI)
/12V_Protected: 12V1.1, C38.1, C39.1, D1.1 (K), D5.2 (A2), J3.1, Q1.2 (S), R7.1, U6.7 (~WAKE), U6.14 (BAT), U7.7 (~WAKE), U7.14 (BAT), U10.3 (~WAKE), U10.7 (VBAT), U11.3 (~WAKE), U11.7 (VBAT)
/12V_Switched: C14.2, C37.2, Q1.3 (D), U8.1 (VIN)
/ESP_EN: C34.1, ESP_FLASH1.3, R16.2, RESET1.2, U3.3 (EN); also elsewhere on the board
/ESP_IO: BOOT1.1, ESP_FLASH1.4, R17.1, U3.25 (IO0); also elsewhere on the board
/GND: 12V1.2, BOOT1.2, C1.1, C2.1, C3.2, C4.1, C5.1, C6.2, C7.2, C8.2, C9.2, C10.2, C11.2, C12.1, C13.1, C14.1, C15.2, C16.2, C17.2, C18.2, C19.2, C20.1, C21.2, C22.2, C23.2, C24.2, C25.2, C26.2, C27.2, C28.2, C29.1, C30.2, C31.2, C32.1, C33.2, C34.2, C35.1, C36.2, C37.1, C38.2, C39.2, C40.1, C41.1, C42.1, C43.1, D2.2 (A), D5.1 (A1), ESP_FLASH1.5, H1.1 (1_1), H3.1 (1_1), H4.1 (1_1), Q2.2 (S), R10.1, R12.1, R13.2, R14.1, R15.2, R18.1, RESET1.1, STM_FLASH1.2, STM_FLASH2.2, U1.12 (VSSA), U1.18 (VSS), U1.63 (VSS), U2.12 (VSSA), U2.18 (VSS), U2.63 (VSS), U3.1 (GND), U3.15 (GND), U3.38 (GND), U3.39 (GND), U3.[1,15,38,39] (GND), U4.2 (GND), U4.8 (S), U5.2 (GND), U5.8 (S), U6.13 (GND), U7.13 (GND), U8.3 (GND), U8.5 (~ON/OFF), U9.1 (GND), U10.5 (GND), U11.5 (GND), Y1.2 (G), Y1.4 (G), Y2.2 (G), Y2.4 (G); also elsewhere on the board
unnamed: C8.1, CAN-FT1.1, R2.1, U6.12 (CANL)
unnamed: C9.1, CAN-FT1.2, R1.1, U6.11 (CANH)
unnamed: C10.1, CAN-FT2.1, R4.1, U7.12 (CANL)
unnamed: C11.1, CAN-FT2.2, R3.1, U7.11 (CANH)
unnamed: CAN-HS1.1, R5.2, U4.6 (CANL)
unnamed: CAN-HS1.2, JP-CAN-HS1.1, U4.7 (CANH)
unnamed: CAN-HS2.1, R6.1, U5.6 (CANL)
unnamed: CAN-HS2.2, JP-CAN-HS2.1, U5.7 (CANH)
unnamed: D1.2 (A), Q1.1 (G), R7.2, R19.2
unnamed: D2.1 (K), L1.1, U8.2 (OUT)
unnamed: D4.2, R11.1
unnamed: D6.3 (BK), R22.1
unnamed: D6.2 (GK), R21.1
unnamed: D6.1 (RK), R20.1
unnamed: ESP_FLASH1.1, U3.35 (TXD0/IO1)
unnamed: ESP_FLASH1.2, U3.34 (RXD0/IO3)
unnamed: J3.2, R11.2
unnamed: JP-CAN-HS1.2, R5.1
unnamed: JP-CAN-HS2.2, R6.2
unnamed: K-LINE1.1, U10.6 (LIN)
unnamed: K-LINE1.2, U11.6 (LIN)
unnamed: Q2.3 (D), R19.1
unnamed: D3.3, D4.3, Q2.1 (G), R10.2
unnamed: STM_FLASH1.3, U1.49 (PA14)
unnamed: C36.1, STM_FLASH1.4, U1.7 (NRST)
unnamed: STM_FLASH1.5, U1.46 (PA13)
unnamed: STM_FLASH2.3, U2.49 (PA14)
unnamed: C35.2, STM_FLASH2.4, U2.7 (NRST)
unnamed: STM_FLASH2.5, U2.46 (PA13)
unnamed: R18.2, U1.60 (BOOT0)
unnamed: U1.16 (PA2), U3.31 (IO19)
unnamed: U1.17 (PA3), U3.30 (IO18)
unnamed: U1.44 (PA11), U6.3 (RXD)
unnamed: U1.45 (PA12), U6.2 (TXD)
unnamed: U1.57 (PB5), U7.3 (RXD)
unnamed: U1.58 (PB6), U7.2 (TXD)
unnamed: R8.1, U1.30 (PB11)
unnamed: R9.1, U1.33 (PB12)
unnamed: R15.1, U1.38 (PC7), U6.5 (~STB)
unnamed: R14.2, U1.39 (PC8), U6.6 (EN)
unnamed: U1.51 (PC10), U2.52 (PC11)
unnamed: U1.52 (PC11), U2.51 (PC10)
unnamed: D3.2, U1.2 (PC13)
unnamed: C41.2, U1.5 (PH0), Y1.1
unnamed: C40.2, U1.6 (PH1), Y1.3
unnamed: C13.2, U1.31 (VCAP_1)
unnamed: C20.2, U1.47 (VCAP_2)
unnamed: C7.1, C25.1, FB1.1, U1.13 (VDDA)
unnamed: R12.2, U2.60 (BOOT0)
unnamed: U2.16 (PA2), U3.28 (IO17)
unnamed: U2.17 (PA3), U3.27 (IO16)
unnamed: U2.44 (PA11), U4.4 (RXD)
unnamed: U2.45 (PA12), U4.1 (TXD)
unnamed: U2.57 (PB5), U5.4 (RXD)
unnamed: U2.58 (PB6), U5.1 (TXD)
unnamed: D3.1, U2.2 (PC13)
unnamed: C42.2, U2.5 (PH0), Y2.1
unnamed: C43.2, U2.6 (PH1), Y2.3
unnamed: C12.2, U2.31 (VCAP_1)
unnamed: C29.2, U2.47 (VCAP_2)
unnamed: C19.1, C28.1, FB2.1, U2.13 (VDDA)
unnamed: R20.2, U3.10 (IO25)
unnamed: R21.2, U3.11 (IO26)
unnamed: R22.2, U3.12 (IO27)
unnamed: D4.1, R13.1, U6.1 (INH)
unnamed: R1.2, U6.8 (RTH)
unnamed: R2.2, U6.9 (RTL)
unnamed: R8.2, U6.4 (~ERR)
unnamed: R3.2, U7.8 (RTH)
unnamed: R4.2, U7.9 (RTL)
unnamed: R9.2, U7.4 (~ERR)
unnamed: U2.38 (PC7), U10.1 (RXD)
unnamed: U2.37 (PC6), U10.4 (TXD)
unnamed: U2.43 (PA10), U11.1 (RXD)
unnamed: U2.42 (PA9), U11.4 (TXD)

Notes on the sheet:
Keepalive LS
Keepalive HS
JP_ALWAYS_ON

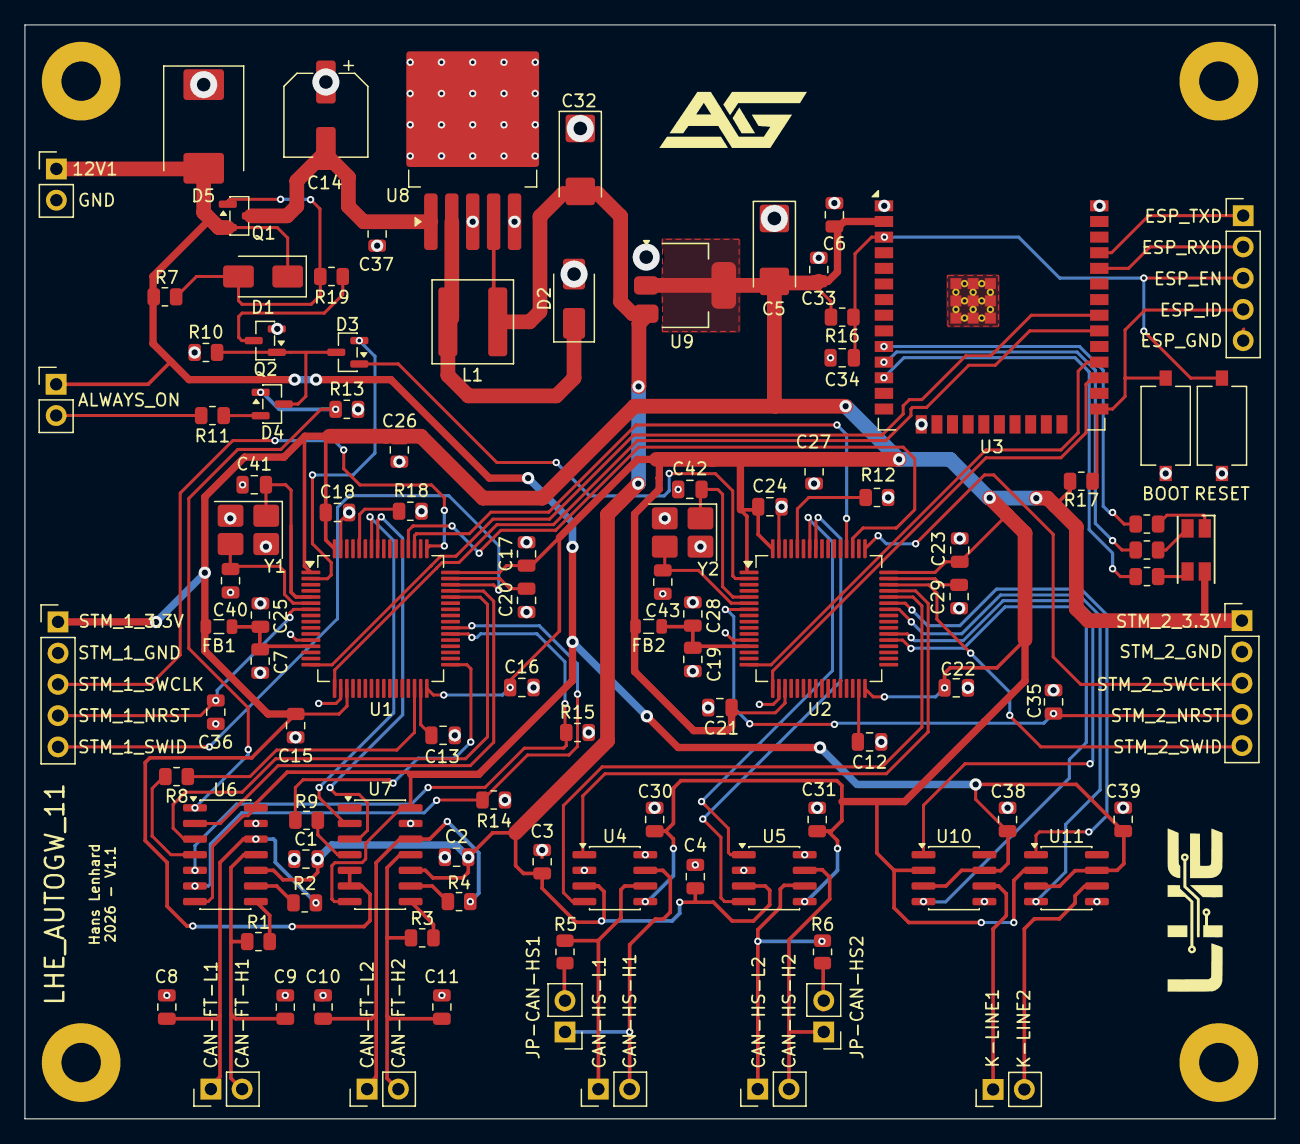
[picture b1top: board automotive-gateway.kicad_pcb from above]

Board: 2 copper layers, 101.6 x 88.9 mm, 107 parts (0 on the bottom side), 82 nets.

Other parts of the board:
BOOT: ESP_BOOT; SW_Tactile_SPST_NO_Straight_CK_PTS636Sx25SMTRLFS
RESET: ESP_RESET; SW_Tactile_SPST_NO_Straight_CK_PTS636Sx25SMTRLFS

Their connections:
/ESP_EN: RESET.2; also elsewhere on the board
/ESP_IO: BOOT.1; also elsewhere on the board
/GND: BOOT.2, RESET.1; also elsewhere on the board
